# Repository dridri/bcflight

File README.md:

# BCFlight

**BCFlight** is an open-source Linux-based Raspberry Pi drone and ground controller system, offering a complete solution for flight control, stabilization, and telemetry.

## Key Features

### Performance
- **Low resource usage** : ~25% CPU and ~100MB RAM on Raspberry Pi 4
- **High frequency** : Sensors and stabilizer update rate up to 8kHz (on RPi4)
- **Ultra-low latency** : ~5ms controls latency, ~50ms video latency over composite
- **Stabilization** : Up to 8 motors with customizable configuration matrix

### Motor Protocols
- **DShot** (150 & 300) - Recommended
- **OneShot125** and **OneShot42**
- **Standard PWM**

### Communication
- **WiFi/Ethernet** : Standard TCP/UDP/IP
- **Raw WiFi** : Based on wifibroadcast
- **Radio** : nRF24L01, SX1276/77/78/79 (FSK/LoRa)
- **S-BUS** : Limited functionality support

### Video & Recording
- **Composite output** : Direct connection to 5GHz VTX modules, with SmartAudio support
- **Multi-camera recording** : MKV format, up to ~120 MPix/s total throughput
- **Gyroflow output** : Compatible with Gyroflow for video stabilization
- **Live HUD** : Real-time telemetry, battery status, speed, acceleration

### Configuration
- **LuaJIT** : Flexible configuration and customizable event handling
- **User code** : Execution of custom Lua functions
- **Full API** : Access to all systems

## Architecture

The project consists of three main components:

### `flight/` - Flight Controller
Core system managing:
- **Main thread** : Sensor data collection, attitude calculation, stabilization
- **Controller thread** : User input reception, telemetry transmission
- **Power thread** : Battery monitoring and current consumption

### `controller_pc/` - PC Interface
Configurable GUI client for:
- Remote control via PC
- Sensor and telemetry visualization
- Advanced configuration

### `controller_rc/` - Remote Control
Portable control interface with:
- Touchscreen support
- Adapted user interface
- Lua configuration

## Supported Sensors

### IMUs
- InvenSense ICM-42605, ICM-20608, MPU-9250, MPU-9150, MPU-6050
- STMicroelectronics L3GD20H, LSM303

### Altimeters/Barometers
- Bosch BMP180, BMP280

### Others
- HC-SR04 (distance sensors)
- ADS1015/ADS1115 (ADC)

## Installation

### Pre-built Images

Automatically generated images based on Raspbian:
- **SSH** : `root:bcflight` by default
- **System** : Read-only by default (security)
- **Flight Service** : Disabled by default for configuration

| Image | Based on | DShot | Analog video |
|-------|-----------|-------|--------------|
| [2023-07-18-raspbian-bcflight.img](https://bcflight.drich.fr/files/2023-07-18-raspbian-bcflight.img) | 2023-05-03-raspios-bullseye-armhf-lite | ✅¹ | ✅¹ |

¹ DShot and composite output can be enabled via `/boot/config.txt` and `/var/flight/config.lua`

### Building from Source

#### PC Controller (Ubuntu/Debian)
```bash
# Dependencies
sudo apt-get install nasm qtmultimedia5-dev qtbase5-dev qtchooser qt5-qmake qtbase5-dev-tools libnl-3-dev libnl-genl-3-dev libnl-route-3-dev libiw-dev libfftw3-dev libqscintilla2-qt5-dev

# Build
git clone https://github.com/dridri/bcflight.git
cd bcflight/controller_pc
cmake -DCMAKE_BUILD_TYPE=Release -S . -B build
cd build && make -j$(nproc)
./controller_pc
```

#### Flight Controller (Raspberry Pi)
```bash
# Dependencies
sudo apt update
sudo apt install git pkg-config cmake make g++ libc6-dev libraspberrypi-dev libiw-dev libdrm-dev libgbm-dev libcamera-dev libgles2-mesa-dev libgps-dev libasound2-dev libcrypt-dev zlib1g-dev libpng-dev libshine-dev libavformat-dev libavutil-dev libavcodec-dev libpigpio-dev lua5.3 libfftw3-dev

# Build
git clone https://github.com/dridri/bcflight
cd bcflight/flight
cmake -Dboard=rpi -Ddebug=1 -S . -B build
cd build && make -j$(nproc)
```

## Configuration

### Basic Configuration Example

```lua
-- Frame configuration (quadcopter)
frame = Multicopter {
    maxspeed = 1.0,
    air_mode = {
        trigger = 0.25,
        speed = 0.15
    },
    motors = {
        DShot( 4 ), DShot( 5 ), DShot( 6 ), DShot( 7 )
    },
    matrix = {
        Vector( -1.0,  1.0, -1.0, 1.0 ),
        Vector(  1.0,  1.0,  1.0, 1.0 ),
        Vector( -1.0, -1.0,  1.0, 1.0 ),
        Vector(  1.0, -1.0, -1.0, 1.0 )
    }
}

-- IMU configuration
imu = IMU {
    gyroscopes = { imu_sensor.gyroscope },
    accelerometers = { imu_sensor.accelerometer },
    filters = {
        rates = { input = Vector( 80, 80, 80 ), output = Vector( 0.25, 0.25, 0.25 ) },
        accelerometer = { input = Vector( 350, 350, 350 ), output = Vector( 0.1, 0.1, 0.1 ) }
    }
}

-- PID stabilizer
stabilizer = Stabilizer {
    loop_time = 500, -- 2000Hz
    rate_speed = 1000, -- deg/sec
    pid_roll = PID( 45, 70, 40 ),
    pid_pitch = PID( 46, 70, 40 ),
    pid_yaw = PID( 45, 90, 2 )
}
```

## Demo

More videos on [YouTube @drichfpv](https://www.youtube.com/@drichfpv/videos)

## User Interface

### PC Controller

### Sensors and Telemetry

## Hardware

### Custom CM4 Carrier Board

**Features:**
- 5V 3A LM22676 regulator (max 42V input)
- ADS1115 ADC for battery voltage measurement
- Dual RFM95W radio sockets with external antennas
- High-precision ICM-42605 IMU
- BMP581 barometer
- Dual CSI camera connectors
- Direct composite video output to VTX

### Hardware Photos

## Documentation

- [Configuration](https://github.com/dridri/bcflight/wiki/Configuration)
- [Sensors](https://github.com/dridri/bcflight/wiki/Sensors)
- [Motors](https://github.com/dridri/bcflight/wiki/Motors)
- [Radio](https://github.com/dridri/bcflight/wiki/Radio)

## Contributing

Contributions are welcome! The project is licensed under GPL v3.

## License

This project is distributed under the GNU General Public License v3.0. See the [LICENSE](LICENSE) file for more details.

## Useful Links

- **CI/CD** : [ci.drich.fr](https://ci.drich.fr/)
- **Images** : [bcflight.drich.fr](https://bcflight.drich.fr/)
- **CAD** : [View on CADLAB.io](https://cadlab.io/project/23184)

---

**⚠️ Warning** : This software is provided for educational and research purposes. Drone usage can be dangerous. Please respect local regulations and use at your own risk.

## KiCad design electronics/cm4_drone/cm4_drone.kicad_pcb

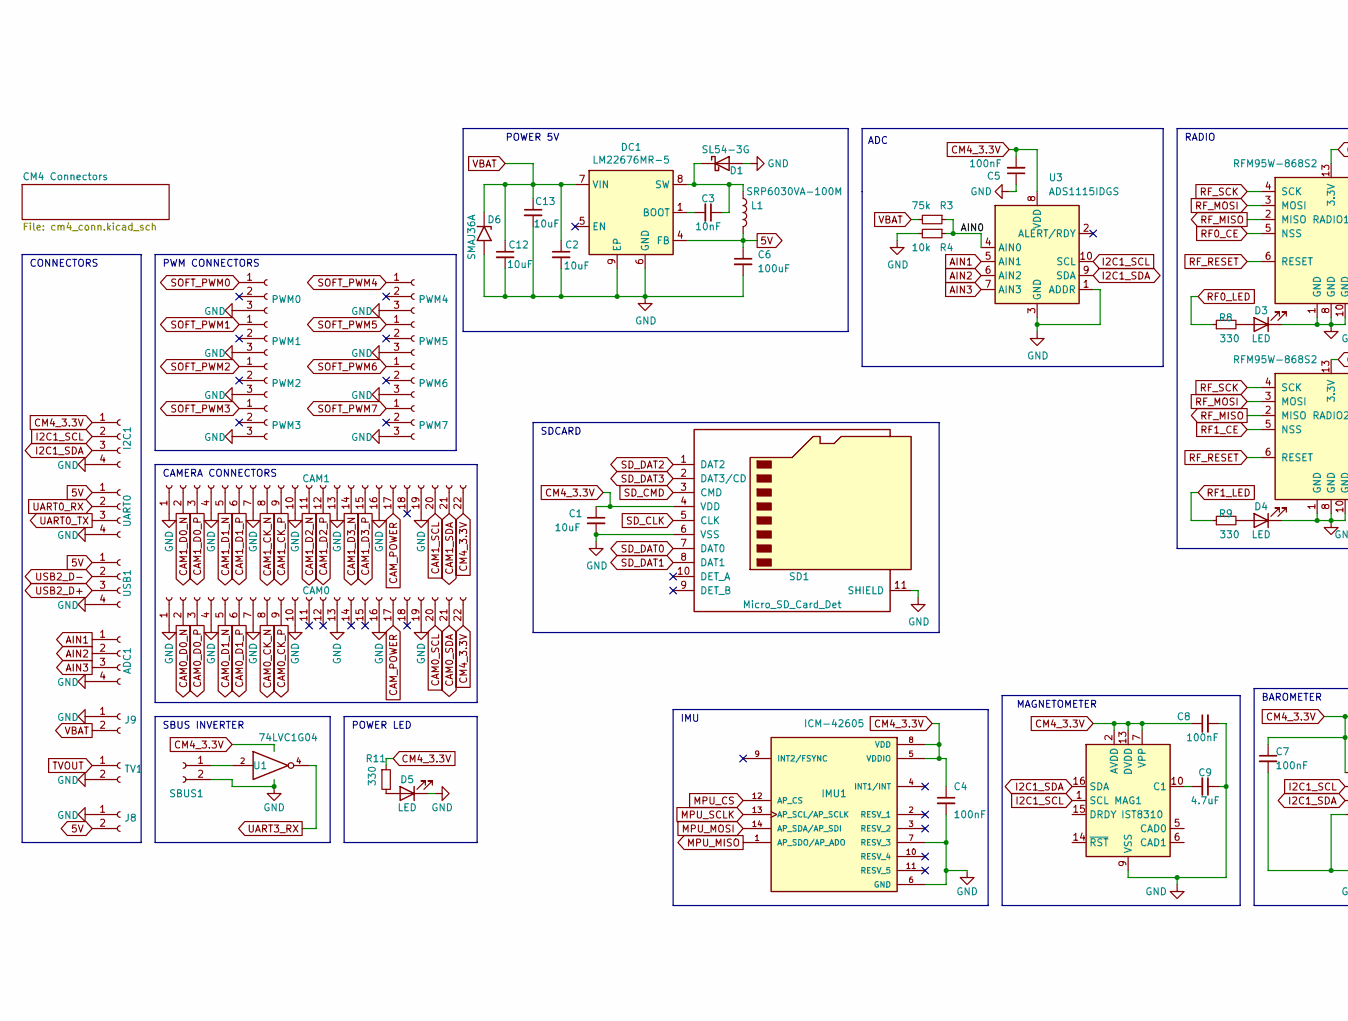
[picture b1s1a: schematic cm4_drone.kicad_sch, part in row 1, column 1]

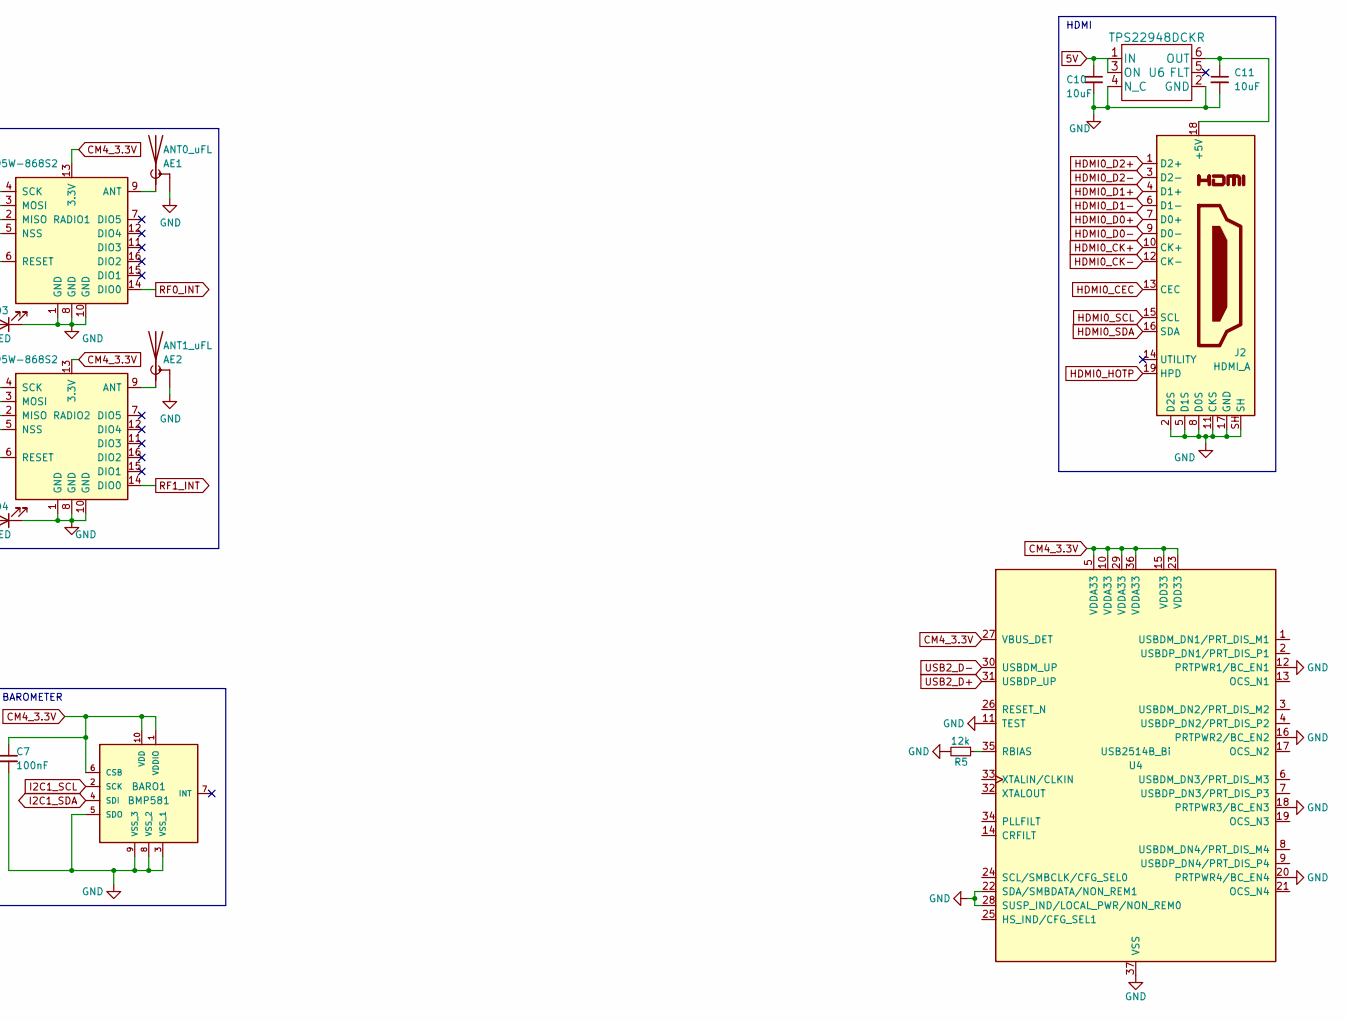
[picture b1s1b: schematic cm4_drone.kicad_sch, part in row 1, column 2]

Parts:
ADC1: Conn_01x04_Female; Breakout_1x04_2mm_SMD
AE1: ANT0_uFL; U.FL_Hirose_U.FL-R-SMT-1_Vertical
AE2: ANT1_uFL; U.FL_Hirose_U.FL-R-SMT-1_Vertical
BARO1: BMP581
C1, C10, C11: 10uF; C_0603_1608Metric
C2, C12, C13: 10uF; C_1206_3216Metric
C3: 10nF; C_0603_1608Metric
C4, C5, C7, C8: 100nF; C_0603_1608Metric
C6: 100uF; C_1206_3216Metric
C9: 4.7uF; C_0603_1608Metric
CAM0, CAM1: Conn_01x22_Female; Hirose_FH12-22S-0.5SH_1x22-1MP_P0.50mm_Horizontal
D1: SL54-3G; D_SMB
D3, D4, D5: LED; LED_0805_2012Metric
D6: SMAJ36A; D_SMA
DC1: LM22676MR-5; TI_SO-PowerPAD-8
I2C1: Conn_01x04_Female; Breakout_1x04_2mm_SMD
IMU1: ICM-42605; PQFN50P300X250X97-14N
J2: HDMI_A; HDMI_Micro-D_Molex_46765-0x01
J8, J9: Conn_01x02_Female; PinHeader_1x02_P2.54mm_Horizontal
L1: SRP6030VA-100M; L_Bourns_SRP7028A_7.3x6.6mm
MAG1: IST8310; LGA-16_3x3mm_P0.5mm
PWM0, PWM1, PWM2, PWM3, PWM4, PWM5, PWM6, PWM7: Conn_01x03_Female; PinHeader_1x03_P2.54mm_Vertical
R3: 75k; R_0603_1608Metric
R4: 10k; R_0603_1608Metric
R5: 12k; R_0603_1608Metric
R8, R9, R11: 330; R_0603_1608Metric
RADIO1, RADIO2: RFM95W-868S2; HOPERF_RFM9XW_SMD
SBUS1: Conn_01x02_Female; Breakout_1x02_2mm_SMD
SD1: Micro_SD_Card_Det; microSD_HC_Hirose_DM3AT-SF-PEJM5
TV1: Conn_01x02_Female; U.FL_Hirose_U.FL-R-SMT-1_Vertical
U1: 74LVC1G04; SOT-23-5
U3: ADS1115IDGS; TSSOP-10_3x3mm_P0.5mm
U4: USB2514B_Bi; QFN-36-1EP_6x6mm_P0.5mm_EP3.7x3.7mm
U6: TPS22948DCKR
UART0: Conn_01x04_Female; Breakout_1x04_2mm_SMD
USB1: Conn_01x04_Female; Breakout_1x04_2mm_SMD

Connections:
5V: C6.1, C10.1, DC1.4 (FB), J8.2, L1.2, U6.1 (IN), U6.3 (ON), UART0.1, USB1.1; also elsewhere on the board
/AIN0: R3.1, R4.1, U3.4 (AIN0)
AIN1: ADC1.1, U3.5 (AIN1)
AIN2: ADC1.2, U3.6 (AIN2)
AIN3: ADC1.3, U3.7 (AIN3)
CAM0_CK_N: CAM0.8; also elsewhere on the board
CAM0_CK_P: CAM0.9; also elsewhere on the board
CAM0_D0_N: CAM0.2; also elsewhere on the board
CAM0_D0_P: CAM0.3; also elsewhere on the board
CAM0_D1_N: CAM0.5; also elsewhere on the board
CAM0_D1_P: CAM0.6; also elsewhere on the board
CAM0_SCL: CAM0.20; also elsewhere on the board
CAM0_SDA: CAM0.21; also elsewhere on the board
CAM1_CK_N: CAM1.8; also elsewhere on the board
CAM1_CK_P: CAM1.9; also elsewhere on the board
CAM1_D0_N: CAM1.2; also elsewhere on the board
CAM1_D0_P: CAM1.3; also elsewhere on the board
CAM1_D1_N: CAM1.5; also elsewhere on the board
CAM1_D1_P: CAM1.6; also elsewhere on the board
CAM1_D2_N: CAM1.11; also elsewhere on the board
CAM1_D2_P: CAM1.12; also elsewhere on the board
CAM1_D3_N: CAM1.14; also elsewhere on the board
CAM1_D3_P: CAM1.15; also elsewhere on the board
CAM1_SCL: CAM1.20; also elsewhere on the board
CAM1_SDA: CAM1.21; also elsewhere on the board
CAM_POWER: CAM0.17, CAM1.17; also elsewhere on the board
CM4_3.3V: BARO1.1 (VDDIO), BARO1.6 (CSB), BARO1.10 (VDD), C1.1, C4.1, C5.2, C7.1, C8.1, CAM0.22, CAM1.22, I2C1.1, IMU1.5 (VDDIO), IMU1.8 (VDD), MAG1.2 (AVDD), MAG1.7 (VPP), MAG1.13 (DVDD), R11.1, RADIO1.13 (3.3V), RADIO2.13 (3.3V), SD1.4 (VDD), U1.5 (VCC), U3.8 (VDD), U4.5 (VDDA33), U4.10 (VDDA33), U4.15 (VDD33), U4.23 (VDD33), U4.27 (VBUS_DET), U4.29 (VDDA33), U4.36 (VDDA33); also elsewhere on the board
GND: ADC1.4, AE1.2 (Shield), AE2.2 (Shield), BARO1.3 (VSS_1), BARO1.5 (SDO), BARO1.8 (VSS_2), BARO1.9 (VSS_3), C1.2, C2.2, C4.2, C5.1, C6.2, C7.2, C8.2, C9.1, C10.2, C11.2, C12.2, C13.2, CAM0.1, CAM0.4, CAM0.7, CAM0.10, CAM0.13, CAM0.16, CAM0.19, CAM1.1, CAM1.4, CAM1.7, CAM1.10, CAM1.13, CAM1.16, CAM1.19, D1.2 (A), D3.1 (K), D4.1 (K), D5.1 (K), D6.2 (A2), DC1.6 (GND), DC1.9 (EP), I2C1.4, IMU1.6 (GND), IMU1.7 (RESV_3), J2.2 (D2S), J2.5 (D1S), J2.8 (D0S), J2.11 (CKS), J2.17 (GND), J2.SH, J8.1, J9.1, MAG1.9 (VSS), MAG1.11 (VSS), PWM0.3, PWM1.3, PWM2.3, PWM3.3, PWM4.3, PWM5.3, PWM6.3, PWM7.3, R4.2, R5.2, RADIO1.1 (GND), RADIO1.8 (GND), RADIO1.10 (GND), RADIO2.1 (GND), RADIO2.8 (GND), RADIO2.10 (GND), SBUS1.2, SD1.6 (VSS), SD1.11 (SHIELD), TV1.2, U1.3 (GND), U3.1 (ADDR), U3.3 (GND), U4.11 (TEST), U4.12 (PRTPWR1/BC_EN1), U4.16 (PRTPWR2/BC_EN2), U4.18 (PRTPWR3/BC_EN3), U4.20 (PRTPWR4/BC_EN4), U4.22 (SDA/SMBDATA/NON_REM1), U4.28 (SUSP_IND/LOCAL_PWR/NON_REM0), U4.37 (VSS), U6.2 (GND), U6.4 (N_C), UART0.4, USB1.4; also elsewhere on the board
I2C1_SCL: BARO1.2 (SCK), I2C1.2, MAG1.1 (SCL), U3.10 (SCL); also elsewhere on the board
I2C1_SDA: BARO1.4 (SDI), I2C1.3, MAG1.16 (SDA), U3.9 (SDA); also elsewhere on the board
MPU_CS: IMU1.12 (AP_CS); also elsewhere on the board
MPU_MISO: IMU1.1 (AP_SDO/AP_ADO); also elsewhere on the board
MPU_MOSI: IMU1.14 (AP_SDA/AP_SDI); also elsewhere on the board
MPU_SCLK: IMU1.13 (AP_SCL/AP_SCLK); also elsewhere on the board
unnamed: AE1.1 (A), RADIO1.9 (ANT)
unnamed: AE2.1 (A), RADIO2.9 (ANT)
unnamed: C11.1, J2.18 (+5V), U6.6 (OUT)
unnamed: C3.1, D1.1 (K), DC1.8 (SW), L1.1
unnamed: D3.2 (A), R8.2
unnamed: D4.2 (A), R9.2
unnamed: D5.2 (A), R11.2
unnamed: C3.2, DC1.1 (BOOT)
unnamed: C9.2, MAG1.10 (C1)
unnamed: R5.1, U4.35 (RBIAS)
unnamed: SBUS1.1, U1.2
PI_PWM0: PWM4.1; also elsewhere on the board
PI_PWM1: PWM5.1; also elsewhere on the board
RF0_CE: RADIO1.5 (NSS); also elsewhere on the board
RF0_INT: RADIO1.14 (DIO0); also elsewhere on the board
RF0_LED: R8.1; also elsewhere on the board
RF1_CE: RADIO2.5 (NSS); also elsewhere on the board
RF1_INT: RADIO2.14 (DIO0); also elsewhere on the board
RF1_LED: R9.1; also elsewhere on the board
RF_MISO: RADIO1.2 (MISO), RADIO2.2 (MISO); also elsewhere on the board
RF_MOSI: RADIO1.3 (MOSI), RADIO2.3 (MOSI); also elsewhere on the board
RF_RESET: RADIO1.6 (RESET), RADIO2.6 (RESET); also elsewhere on the board
RF_SCK: RADIO1.4 (SCK), RADIO2.4 (SCK); also elsewhere on the board
SD_CLK: SD1.5 (CLK); also elsewhere on the board
SD_CMD: SD1.3 (CMD); also elsewhere on the board
SD_DAT0: SD1.7 (DAT0); also elsewhere on the board
SD_DAT1: SD1.8 (DAT1); also elsewhere on the board
SD_DAT2: SD1.1 (DAT2); also elsewhere on the board
SD_DAT3: SD1.2 (DAT3/CD); also elsewhere on the board
SOFT_PWM0: PWM0.1; also elsewhere on the board
SOFT_PWM1: PWM1.1, U1.4; also elsewhere on the board
SOFT_PWM2: PWM2.1; also elsewhere on the board
SOFT_PWM3: PWM3.1; also elsewhere on the board
SOFT_PWM6: PWM6.1; also elsewhere on the board
SOFT_PWM7: PWM7.1; also elsewhere on the board
TVOUT: TV1.1; also elsewhere on the board
UART0_RX: UART0.2; also elsewhere on the board
UART0_TX: UART0.3; also elsewhere on the board
USB2_D+: U4.31 (USBDP_UP), USB1.3; also elsewhere on the board
USB2_D-: U4.30 (USBDM_UP), USB1.2; also elsewhere on the board
VBAT: C2.1, C12.1, C13.1, D6.1 (A1), DC1.7 (VIN), J9.2, R3.2

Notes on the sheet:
RADIO
CAMERA CONNECTORS
CONNECTORS
POWER 5V
PWM CONNECTORS
HDMI
SDCARD
POWER LED
SBUS INVERTER
MAGNETOMETER
IMU
ADC
BAROMETER

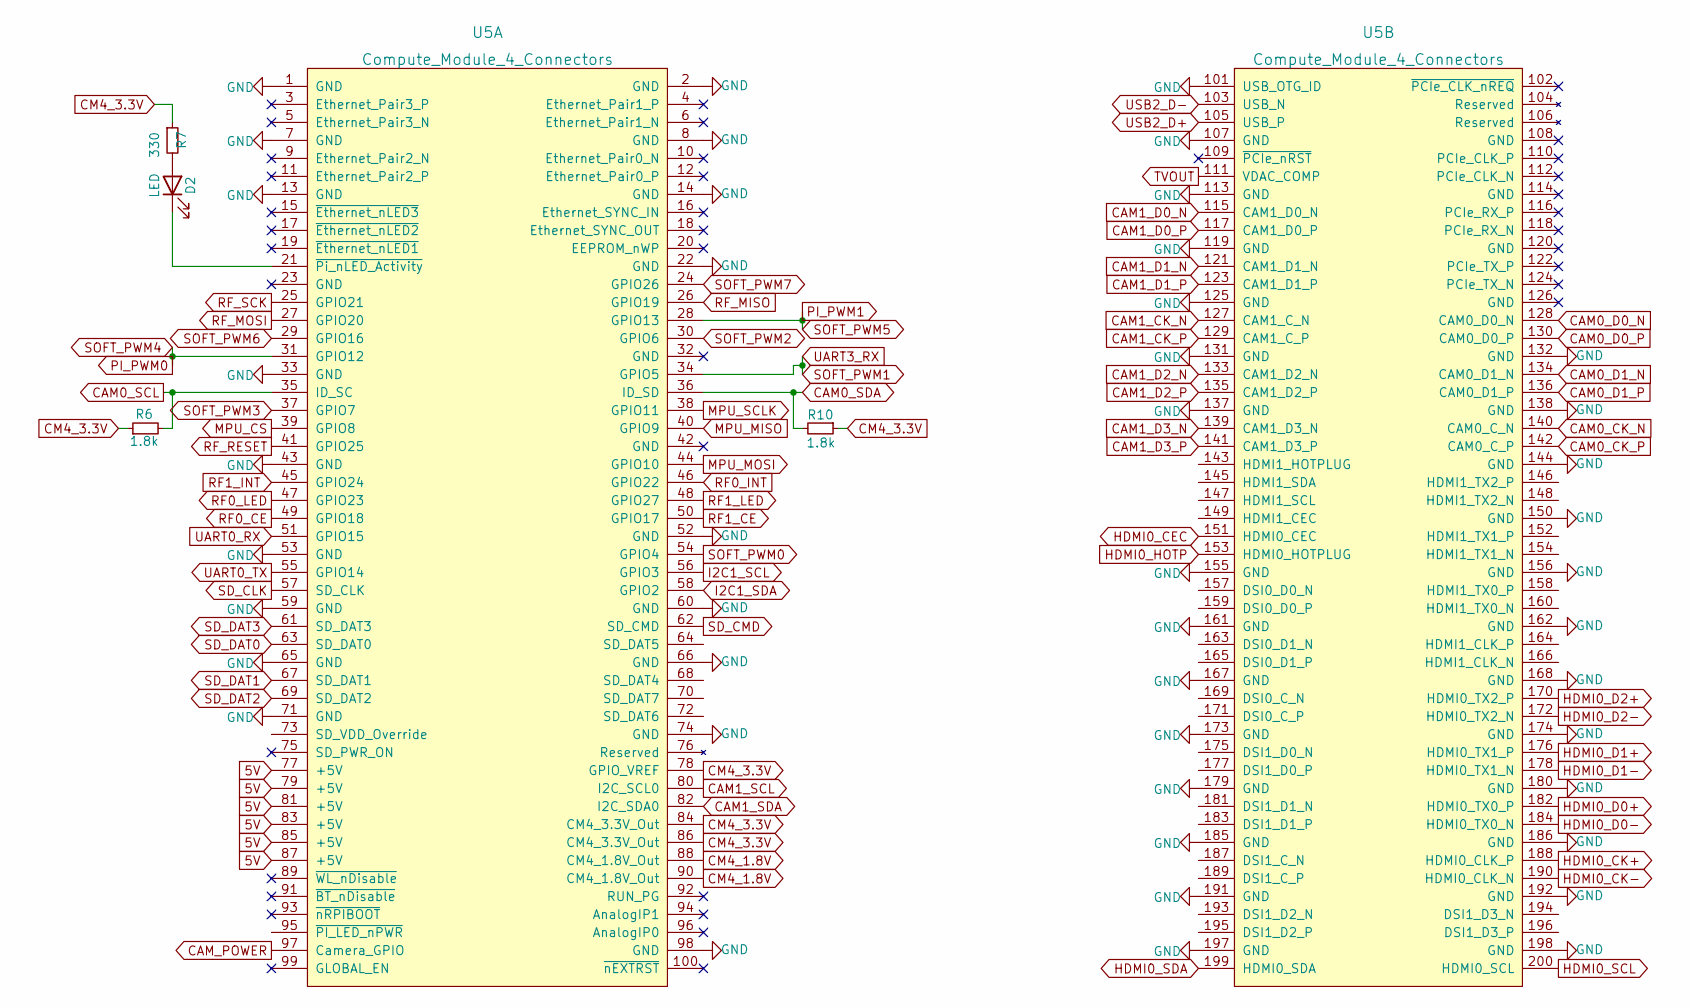
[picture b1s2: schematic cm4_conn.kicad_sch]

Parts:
D2: LED; LED_0805_2012Metric
R6, R10: 1.8k; R_0603_1608Metric
R7: 330; R_0603_1608Metric
U5: Compute_Module_4_Connectors; Raspberry-Pi-4-Compute-Module

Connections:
5V: U5.77 (+5V), U5.79 (+5V), U5.81 (+5V), U5.83 (+5V), U5.85 (+5V), U5.87 (+5V); also elsewhere on the board
CAM0_CK_N: U5.140 (CAM0_C_N); also elsewhere on the board
CAM0_CK_P: U5.142 (CAM0_C_P); also elsewhere on the board
CAM0_D0_N: U5.128 (CAM0_D0_N); also elsewhere on the board
CAM0_D0_P: U5.130 (CAM0_D0_P); also elsewhere on the board
CAM0_D1_N: U5.134 (CAM0_D1_N); also elsewhere on the board
CAM0_D1_P: U5.136 (CAM0_D1_P); also elsewhere on the board
CAM0_SCL: R6.2, U5.35 (ID_SC); also elsewhere on the board
CAM0_SDA: R10.2, U5.36 (ID_SD); also elsewhere on the board
CAM1_CK_N: U5.127 (CAM1_C_N); also elsewhere on the board
CAM1_CK_P: U5.129 (CAM1_C_P); also elsewhere on the board
CAM1_D0_N: U5.115 (CAM1_D0_N); also elsewhere on the board
CAM1_D0_P: U5.117 (CAM1_D0_P); also elsewhere on the board
CAM1_D1_N: U5.121 (CAM1_D1_N); also elsewhere on the board
CAM1_D1_P: U5.123 (CAM1_D1_P); also elsewhere on the board
CAM1_D2_N: U5.133 (CAM1_D2_N); also elsewhere on the board
CAM1_D2_P: U5.135 (CAM1_D2_P); also elsewhere on the board
CAM1_D3_N: U5.139 (CAM1_D3_N); also elsewhere on the board
CAM1_D3_P: U5.141 (CAM1_D3_P); also elsewhere on the board
CAM1_SCL: U5.80 (I2C_SCL0); also elsewhere on the board
CAM1_SDA: U5.82 (I2C_SDA0); also elsewhere on the board
CAM_POWER: U5.97 (Camera_GPIO); also elsewhere on the board
CM4_1.8V: U5.88 (CM4_1.8V_Out), U5.90 (CM4_1.8V_Out)
CM4_3.3V: R6.1, R7.1, R10.1, U5.78 (GPIO_VREF), U5.84 (CM4_3.3V_Out), U5.86 (CM4_3.3V_Out); also elsewhere on the board
GND: U5.1 (GND), U5.2 (GND), U5.7 (GND), U5.8 (GND), U5.13 (GND), U5.14 (GND), U5.22 (GND), U5.33 (GND), U5.43 (GND), U5.52 (GND), U5.53 (GND), U5.59 (GND), U5.60 (GND), U5.65 (GND), U5.66 (GND), U5.71 (GND), U5.74 (GND), U5.98 (GND), U5.101 (USB_OTG_ID), U5.107 (GND), U5.113 (GND), U5.119 (GND), U5.125 (GND), U5.131 (GND), U5.132 (GND), U5.137 (GND), U5.138 (GND), U5.144 (GND), U5.150 (GND), U5.155 (GND), U5.156 (GND), U5.161 (GND), U5.162 (GND), U5.167 (GND), U5.168 (GND), U5.173 (GND), U5.174 (GND), U5.179 (GND), U5.180 (GND), U5.185 (GND), U5.186 (GND), U5.191 (GND), U5.192 (GND), U5.197 (GND), U5.198 (GND); also elsewhere on the board
HDMI0_CEC: U5.151 (HDMI0_CEC)
HDMI0_CK+: U5.188 (HDMI0_CLK_P)
HDMI0_CK-: U5.190 (HDMI0_CLK_N)
HDMI0_D0+: U5.182 (HDMI0_TX0_P)
HDMI0_D0-: U5.184 (HDMI0_TX0_N)
HDMI0_D1+: U5.176 (HDMI0_TX1_P)
HDMI0_D1-: U5.178 (HDMI0_TX1_N)
HDMI0_D2+: U5.170 (HDMI0_TX2_P)
HDMI0_D2-: U5.172 (HDMI0_TX2_N)
HDMI0_HOTP: U5.153 (HDMI0_HOTPLUG)
HDMI0_SCL: U5.200 (HDMI0_SCL)
HDMI0_SDA: U5.199 (HDMI0_SDA)
I2C1_SCL: U5.56 (GPIO3); also elsewhere on the board
I2C1_SDA: U5.58 (GPIO2); also elsewhere on the board
MPU_CS: U5.39 (GPIO8); also elsewhere on the board
MPU_MISO: U5.40 (GPIO9); also elsewhere on the board
MPU_MOSI: U5.44 (GPIO10); also elsewhere on the board
MPU_SCLK: U5.38 (GPIO11); also elsewhere on the board
unnamed: D2.2 (A), R7.2
unnamed: D2.1 (K), U5.21 (~Pi_nLED_Activity)
PI_PWM0: U5.31 (GPIO12); also elsewhere on the board
PI_PWM1: U5.28 (GPIO13); also elsewhere on the board
RF0_CE: U5.49 (GPIO18); also elsewhere on the board
RF0_INT: U5.46 (GPIO22); also elsewhere on the board
RF0_LED: U5.47 (GPIO23); also elsewhere on the board
RF1_CE: U5.50 (GPIO17); also elsewhere on the board
RF1_INT: U5.45 (GPIO24); also elsewhere on the board
RF1_LED: U5.48 (GPIO27); also elsewhere on the board
RF_MISO: U5.26 (GPIO19); also elsewhere on the board
RF_MOSI: U5.27 (GPIO20); also elsewhere on the board
RF_RESET: U5.41 (GPIO25); also elsewhere on the board
RF_SCK: U5.25 (GPIO21); also elsewhere on the board
SD_CLK: U5.57 (SD_CLK); also elsewhere on the board
SD_CMD: U5.62 (SD_CMD); also elsewhere on the board
SD_DAT0: U5.63 (SD_DAT0); also elsewhere on the board
SD_DAT1: U5.67 (SD_DAT1); also elsewhere on the board
SD_DAT2: U5.69 (SD_DAT2); also elsewhere on the board
SD_DAT3: U5.61 (SD_DAT3); also elsewhere on the board
SOFT_PWM0: U5.54 (GPIO4); also elsewhere on the board
SOFT_PWM1: U5.34 (GPIO5); also elsewhere on the board
SOFT_PWM2: U5.30 (GPIO6); also elsewhere on the board
SOFT_PWM3: U5.37 (GPIO7); also elsewhere on the board
SOFT_PWM6: U5.29 (GPIO16); also elsewhere on the board
SOFT_PWM7: U5.24 (GPIO26); also elsewhere on the board
TVOUT: U5.111 (VDAC_COMP); also elsewhere on the board
UART0_RX: U5.51 (GPIO15); also elsewhere on the board
UART0_TX: U5.55 (GPIO14); also elsewhere on the board
USB2_D+: U5.105 (USB_P); also elsewhere on the board
USB2_D-: U5.103 (USB_N); also elsewhere on the board

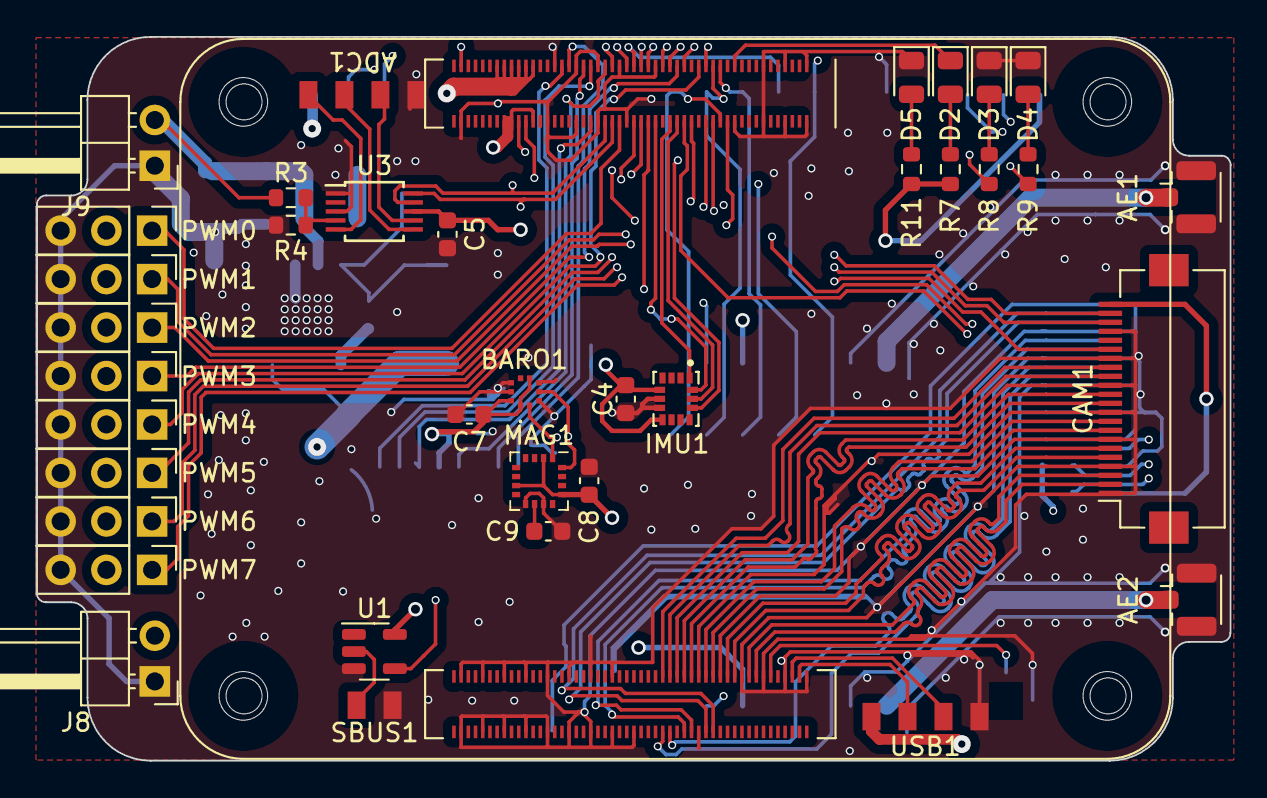
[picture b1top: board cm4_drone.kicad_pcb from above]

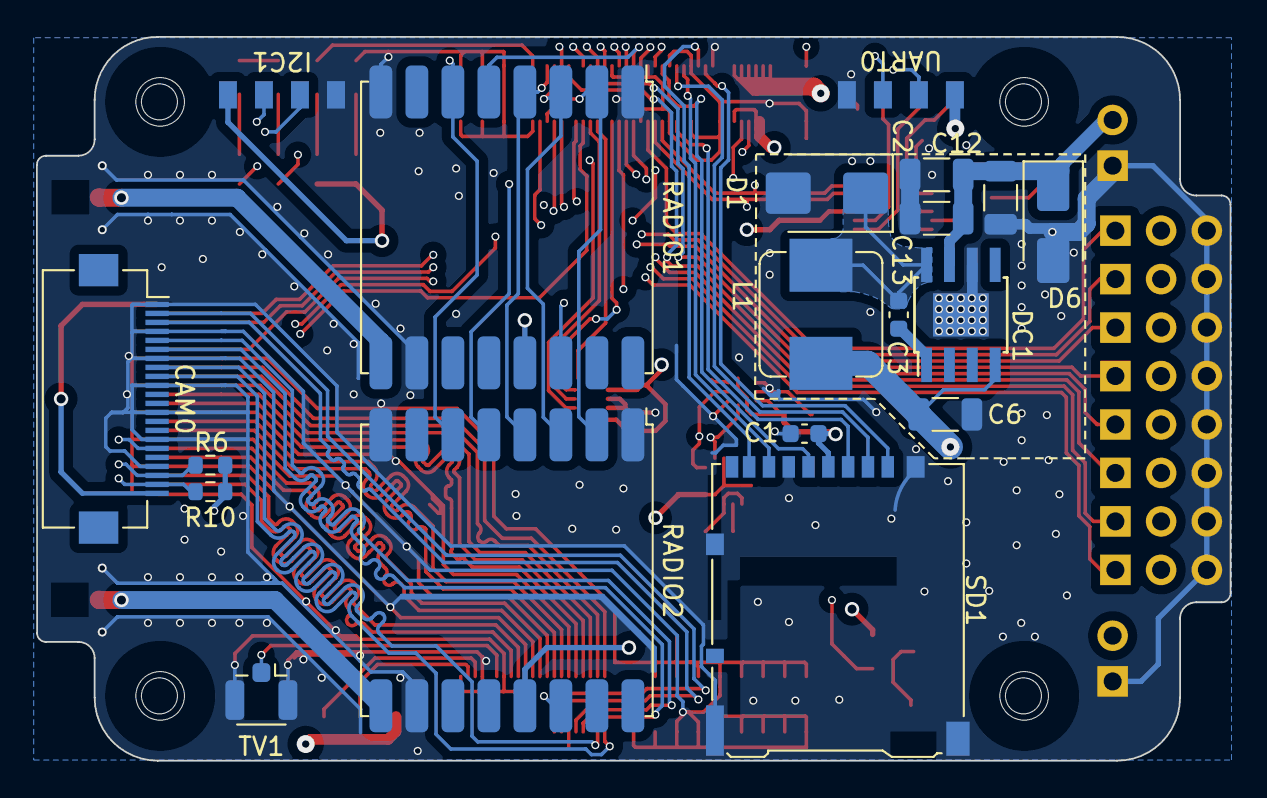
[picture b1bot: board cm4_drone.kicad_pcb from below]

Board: 4 copper layers, 66.3 x 40.2 mm, 56 parts (19 on the bottom side), 76 nets.

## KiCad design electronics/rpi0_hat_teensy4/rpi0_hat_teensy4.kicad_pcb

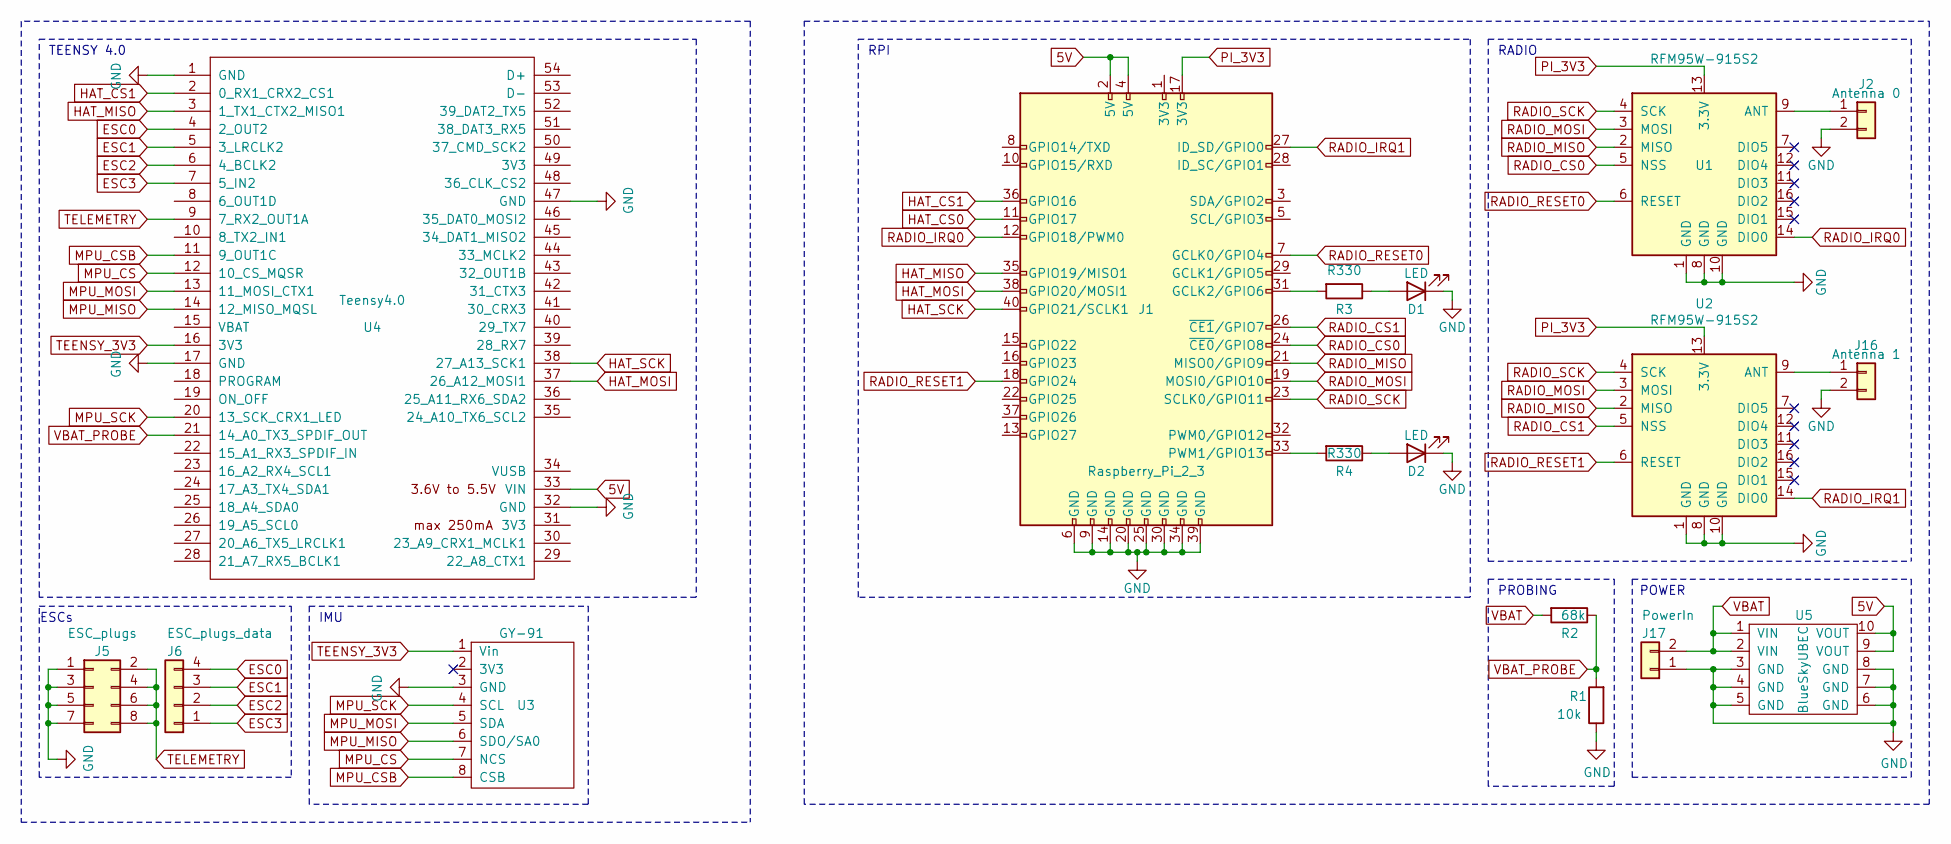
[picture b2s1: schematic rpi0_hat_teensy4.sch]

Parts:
D1, D2: LED; LED_0805_2012Metric_Pad1.15x1.40mm_HandSolder
J1: Raspberry_Pi_2_3; PinSocket_2x20_P2.54mm_Vertical
J2: Antenna 0; U.FL_Hirose_U.FL-R-SMT-1_Vertical
J5: ESC_plugs; PinHeader_2x04_P2.54mm_Vertical
J6: ESC_plugs_data; PinHeader_1x04_P2.54mm_Vertical
J16: Antenna 1; U.FL_Hirose_U.FL-R-SMT-1_Vertical
J17: PowerIn; JST_XH_SMD_1x02_P2.50mm_Horizontal
R1: 10k; R_0805_2012Metric_Pad1.15x1.40mm_HandSolder
R2: 68k; R_0805_2012Metric_Pad1.15x1.40mm_HandSolder
R3, R4: R330; R_0805_2012Metric_Pad1.15x1.40mm_HandSolder
U1, U2: RFM95W-915S2; HOPERF_RFM9XW_SMD
U3: GY-91
U4: Teensy4.0; Teensy40
U5: BlueSkyUBEC

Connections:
5V: J1.2 (5V), J1.4 (5V), U4.33 (VIN), U5.9 (VOUT), U5.10 (VOUT)
ESC0: J6.4, U4.4 (2_OUT2)
ESC1: J6.3, U4.5 (3_LRCLK2)
ESC2: J6.2, U4.6 (4_BCLK2)
ESC3: J6.1, U4.7 (5_IN2)
GND: D1.1 (K), D2.1 (K), J1.6 (GND), J1.9 (GND), J1.14 (GND), J1.20 (GND), J1.25 (GND), J1.30 (GND), J1.34 (GND), J1.39 (GND), J2.2, J5.1, J5.3, J5.5, J5.7, J16.2, J17.1, R1.1, U1.1 (GND), U1.8 (GND), U1.10 (GND), U2.1 (GND), U2.8 (GND), U2.10 (GND), U3.3 (GND), U4.1 (GND), U4.17 (GND), U4.32 (GND), U4.47 (GND), U5.3 (GND), U5.4 (GND), U5.5 (GND), U5.6 (GND), U5.7 (GND), U5.8 (GND)
HAT_CS0: J1.11 (GPIO17)
HAT_CS1: J1.36 (GPIO16), U4.2 (0_RX1_CRX2_CS1)
HAT_MISO: J1.35 (GPIO19/MISO1), U4.3 (1_TX1_CTX2_MISO1)
HAT_MOSI: J1.38 (GPIO20/MOSI1), U4.37 (26_A12_MOSI1)
HAT_SCK: J1.40 (GPIO21/SCLK1), U4.38 (27_A13_SCK1)
MPU_CS: U3.7 (NCS), U4.12 (10_CS_MQSR)
MPU_CSB: U3.8 (CSB), U4.11 (9_OUT1C)
MPU_MISO: U3.6 (SDO/SA0), U4.14 (12_MISO_MQSL)
MPU_MOSI: U3.5 (SDA), U4.13 (11_MOSI_CTX1)
MPU_SCK: U3.4 (SCL), U4.20 (13_SCK_CRX1_LED)
unnamed: D1.2 (A), R3.1
unnamed: D2.2 (A), R4.1
unnamed: J1.31 (GCLK2/GPIO6), R3.2
unnamed: J1.33 (PWM1/GPIO13), R4.2
unnamed: J2.1, U1.9 (ANT)
unnamed: J16.1, U2.9 (ANT)
PI_3V3: J1.17 (3V3), U1.13 (3.3V), U2.13 (3.3V)
RADIO_CS0: J1.24 (~CE0~/GPIO8), U1.5 (NSS)
RADIO_CS1: J1.26 (~CE1~/GPIO7), U2.5 (NSS)
RADIO_IRQ0: J1.12 (GPIO18/PWM0), U1.14 (DIO0)
RADIO_IRQ1: J1.27 (ID_SD/GPIO0), U2.14 (DIO0)
RADIO_MISO: J1.21 (MISO0/GPIO9), U1.2 (MISO), U2.2 (MISO)
RADIO_MOSI: J1.19 (MOSI0/GPIO10), U1.3 (MOSI), U2.3 (MOSI)
RADIO_RESET0: J1.7 (GCLK0/GPIO4), U1.6 (RESET)
RADIO_RESET1: J1.18 (GPIO24), U2.6 (RESET)
RADIO_SCK: J1.23 (SCLK0/GPIO11), U1.4 (SCK), U2.4 (SCK)
TEENSY_3V3: U3.1 (Vin), U4.16 (3V3)
TELEMETRY: J5.2, J5.4, J5.6, J5.8, U4.9 (7_RX2_OUT1A)
VBAT: J17.2, R2.2, U5.1 (VIN), U5.2 (VIN)
VBAT_PROBE: R1.2, R2.1, U4.21 (14_A0_TX3_SPDIF_OUT)

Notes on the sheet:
POWER
IMU
RADIO
PROBING
ESCs
RPI
TEENSY 4.0

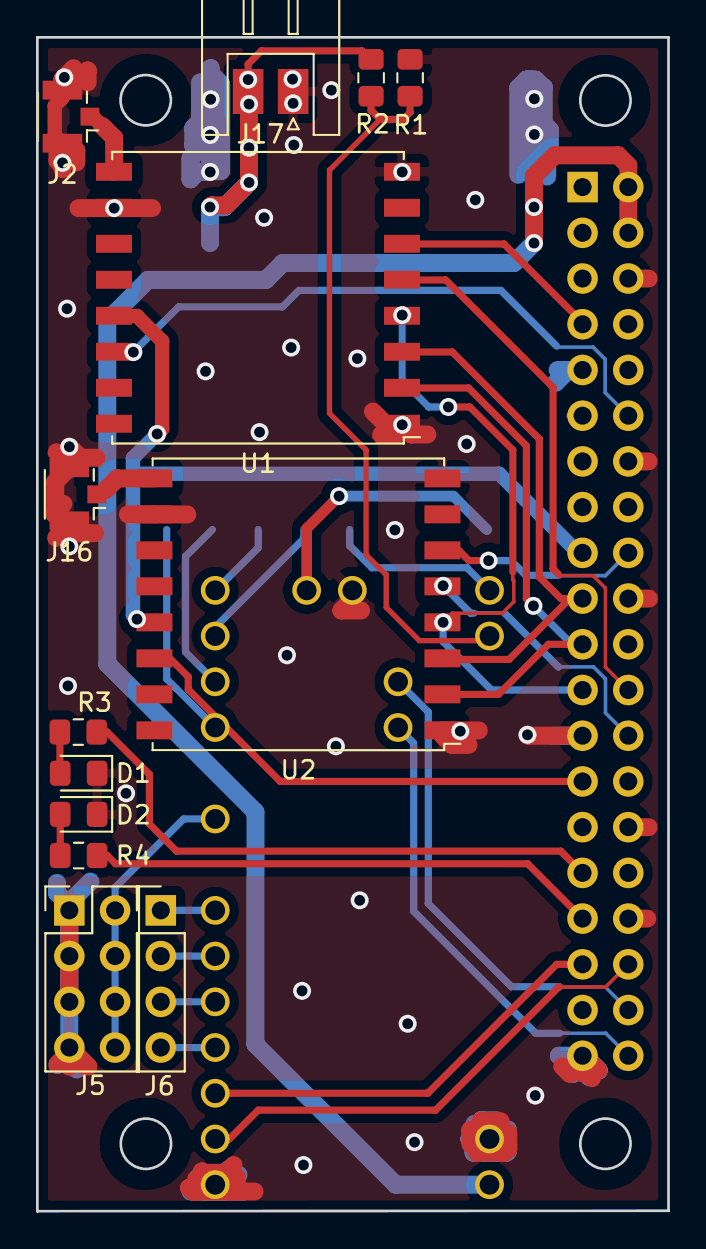
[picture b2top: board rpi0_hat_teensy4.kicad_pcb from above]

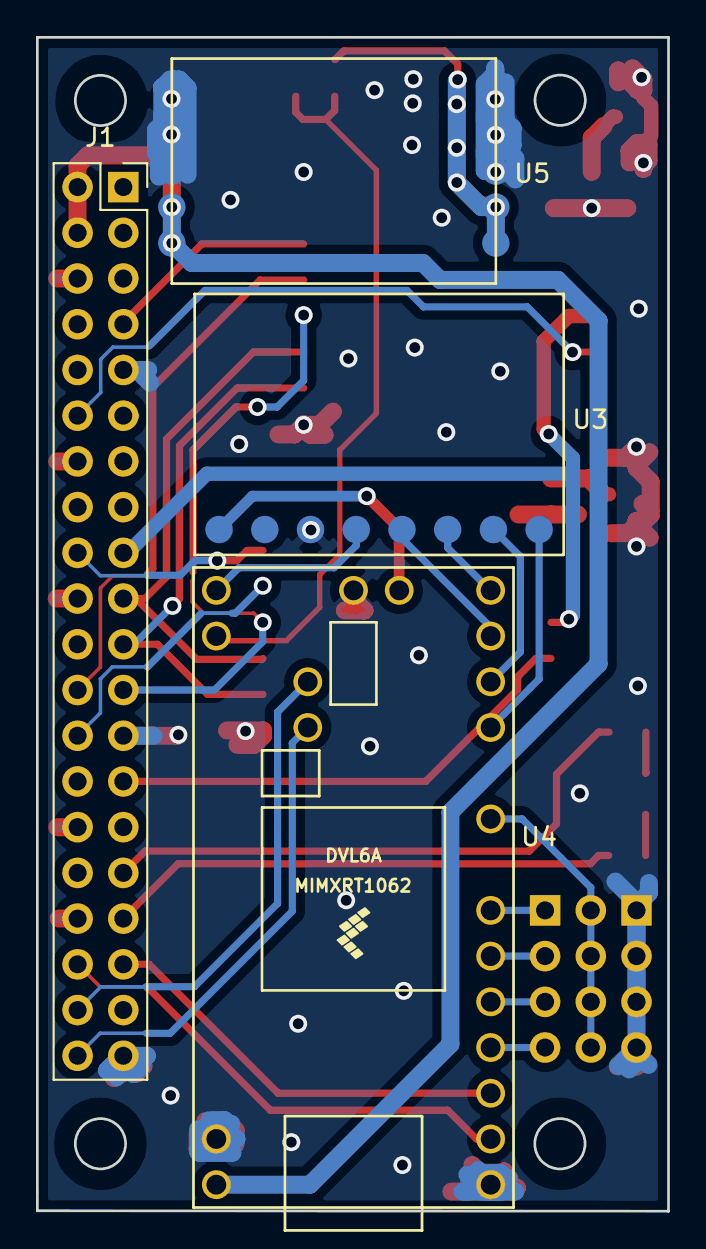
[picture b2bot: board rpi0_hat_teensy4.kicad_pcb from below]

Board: 2 copper layers, 35.1 x 65.2 mm, 17 parts (4 on the bottom side), 35 nets.

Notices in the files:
README.md:
License: GPL v3
